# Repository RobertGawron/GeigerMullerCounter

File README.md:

# GeigerMullerCounter

## Purpose

The Geiger–Müller counter is a simple, reliable tool designed to measure ionizing radiation. It is widely used in experiments, radiation detection, and environmental monitoring.

## Principle of Operation
When a high voltage (typically 380–420V) is applied to the Geiger–Müller tube, the tube does not conduct electricity under normal conditions. However, when a radiation particle interacts with the tube, it briefly conducts a current, producing a pulse. These pulses are counted by the detector, and the number of pulses in a given time interval (typically 20 seconds to 2.5 minutes) is proportional to the level of ionizing radiation.

## Final Version
Below is an image of the device (the green PCB in the center). Other components in the image are not relevant to this project, as they belong to the [Cosmic Ray Detector](https://github.com/RobertGawron/CosmicRayDetector), where the Geiger counter is used as a building block.

## System Architecture

The diagram shows the main components and how they interact. The component IDs in parentheses match those in the circuit diagram below, making it easier to understand the circuit.

Tools: PlantUML

## Hardware 

The circuit is shown below. For a full-size image, right-click and open it in a new tab.

Tools: KiCad (for PCB design).

More info can be fond in [here](Hardware/GeigerMullerCounter/README.md).

## Software

Data from the Geiger–Müller counter is collected and managed using the [HardwareDataLogger](https://github.com/RobertGawron/HardwareDataLogger), which is built around an STM32 microcontroller for data collection, display, and storage (via SD card), and an ESP8266 for WiFi communication.

Tools: C++, Python.

## Experiments Conducted

* [Measuring Nuclear Radiation of Potassium from Cigarette Ashes](https://robertgawron.blogspot.com/2015/07/measuring-radioactivity-of-potassium.html): Cigarette ashes are the burnt remains of tobacco leaves, which are rich in potassium. In natural environments, potassium contains the radioactive isotope potassium-40 (K-40), which contributes to the measured radiation levels.
* [Cosmic Ray Detector](https://github.com/RobertGawron/CosmicRayDetector): a device designed to detect high-energy particles, known as cosmic rays, that originate from outer space.
* [Trip to Śnieżka mountain to measure radioactivity levels](https://robertgawron.blogspot.com/2015/06/a-trip-with-geiger-counter-on-sniezka.html): mountains naturally have elevated radiation levels due to increased cosmic rays and radioactive minerals in the rocks. Additionally, near Śnieżka Mountain, a Cold War-era uranium mine in Kowary contributed to the region's historical radiation levels.

## Safety Hazards

**Warning: The device operates at high voltage (380–420V). Contact with the PCB or Geiger tube while powered can cause electric shocks, injuries, or even death. Do not touch any components while the device is powered on.**

## License
This project is licensed under the MIT License. See the [LICENSE](./LICENSE) file for details.

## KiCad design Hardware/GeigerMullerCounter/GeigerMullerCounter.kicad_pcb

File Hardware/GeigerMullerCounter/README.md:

## Introduction

For more details about the hardware design and implementation, visit my [blog post on the Geiger–Müller counter](http://robertgawron.blogspot.com/2015/02/homemade-geigermuller-counter-part-i.html).

# Remarks

Depending on the coil you used, you may need to adjust R3, R4, and R5. If the voltage is too low, try decreasing R4 first.

## KiCad Configuration

To ensure proper alignment and design consistency in KiCad, configure the grid settings as shown below:

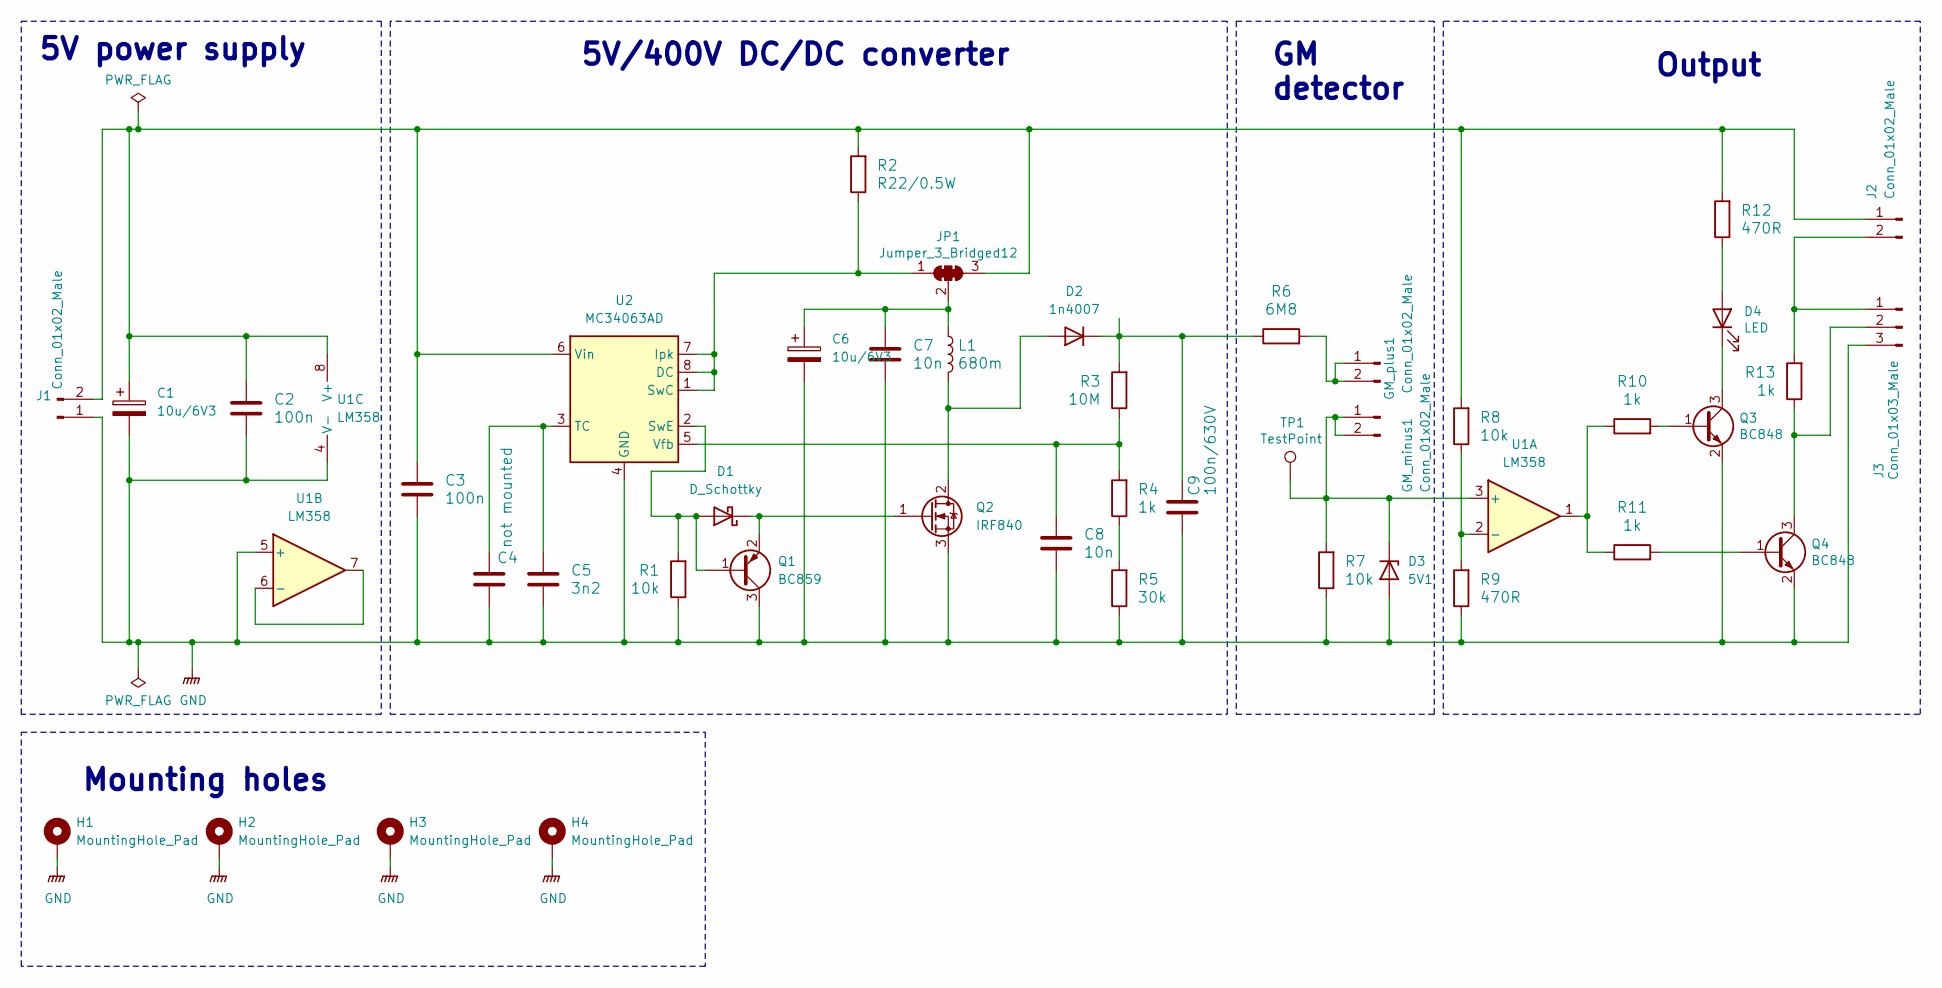
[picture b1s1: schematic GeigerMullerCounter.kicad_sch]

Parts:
C1, C6: 10u/6V3; CP_EIA-3528-21_Kemet-B
C2, C3: 100n; C_0805_2012Metric
C4: not mounted; C_0805_2012Metric
C5: 3n2; C_0805_2012Metric
C7, C8: 10n; C_0805_2012Metric
C9: 100n/630V; C_Rect_L13.5mm_W5.0mm_P10.00mm_FKS3_FKP3_MKS4
D1: D_Schottky; D_SOT-23_ANK
D2: 1n4007; D_DO-41_SOD81_P7.62mm_Horizontal
D3: 5V1; D_A-405_P2.54mm_Vertical_KathodeUp
D4: LED; LED_0805_2012Metric
GM_minus1: Conn_01x02_Male; Pin_Header_Straight_1x02_Pitch2.54mm
GM_plus1: Conn_01x02_Male; Pin_Header_Straight_1x02_Pitch2.54mm
H1, H2, H3, H4: MountingHole_Pad; MountingHole_3.5mm_Pad
J1, J2: Conn_01x02_Male; PinHeader_1x02_P2.54mm_Vertical
J3: Conn_01x03_Male; PinHeader_1x03_P2.54mm_Vertical
JP1: Jumper_3_Bridged12; SolderJumper-3_P1.3mm_Bridged12_Pad1.0x1.5mm
L1: 680m; L_Radial_D7.5mm_P5.00mm_Fastron_07P
Q1: BC859; TSOT-23
Q2: IRF840; TO-220-3_Vertical
Q3, Q4: BC848; SOT-23
R1, R8: 10k; R_0805_2012Metric
R2: R22/0.5W; R_Axial_DIN0207_L6.3mm_D2.5mm_P2.54mm_Vertical
R3: 10M; R_Axial_DIN0207_L6.3mm_D2.5mm_P5.08mm_Vertical
R4, R10, R11, R13: 1k; R_0805_2012Metric
R5: 30k; R_0805_2012Metric
R6: 6M8; R_Axial_DIN0207_L6.3mm_D2.5mm_P7.62mm_Horizontal
R7: 10k; R_0805_2012Metric_Pad1.15x1.40mm_HandSolder
R9, R12: 470R; R_0805_2012Metric
TP1: TestPoint; TestPoint_Pad_D1.5mm
U1: LM358; SO-8_5.3x6.2mm_P1.27mm
U2: MC34063AD; SO-8_5.3x6.2mm_P1.27mm

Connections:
GND: C1.2, C2.2, C3.2, C4.2, C5.2, C6.2, C7.2, C8.2, C9.2, D3.2 (A), H1.1, H2.1, H3.1, H4.1, J1.1, J3.3, Q1.3 (C), Q2.3 (S), Q3.2 (E), Q4.2 (E), R1.1, R5.1, R7.1, R9.1, U1.4 (V-), U1.5 (+), U2.4 (GND)
unnamed: D1.2 (A), Q1.1 (B), R1.2, U2.2 (SwE)
unnamed: D1.1 (K), Q1.2 (E), Q2.1 (G)
unnamed: D2.2 (A), L1.2, Q2.2 (D)
unnamed: C9.1, D2.1 (K), R3.2, R6.1
unnamed: D3.1 (K), GM_minus1.1, GM_minus1.2, R7.2, TP1.1, U1.3 (+)
unnamed: D4.2 (A), R12.1
unnamed: D4.1 (K), Q3.3 (C)
unnamed: GM_plus1.1, GM_plus1.2, R6.2
unnamed: C1.1, C2.1, C3.1, J1.2, J2.1, JP1.3 (B), R2.2, R8.2, R12.2, U1.8 (V+), U2.6 (Vin)
unnamed: J2.2, J3.1, R13.2
unnamed: J3.2, Q4.3 (C), R13.1
unnamed: JP1.1 (A), R2.1, U2.1 (SwC), U2.7 (Ipk), U2.8 (DC)
unnamed: C6.1, C7.1, JP1.2 (C), L1.1
unnamed: Q3.1 (B), R10.2
unnamed: Q4.1 (B), R11.2
unnamed: R4.1, R5.2
unnamed: R10.1, R11.1, U1.1
unnamed: R8.1, R9.2, U1.2 (-)
unnamed: U1.6 (-), U1.7
unnamed: C4.1, C5.1, U2.3 (TC)
unnamed: C8.1, R3.1, R4.2, U2.5 (Vfb)

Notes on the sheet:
Mounting holes
Output
5V/400V DC/DC converter
GM detector
5V power supply

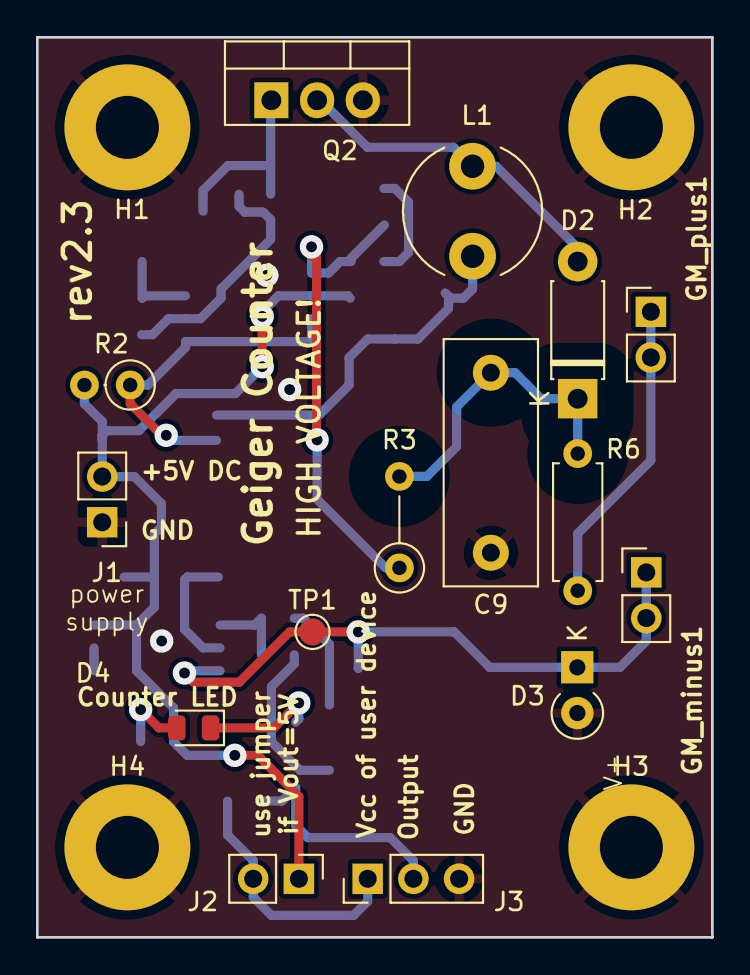
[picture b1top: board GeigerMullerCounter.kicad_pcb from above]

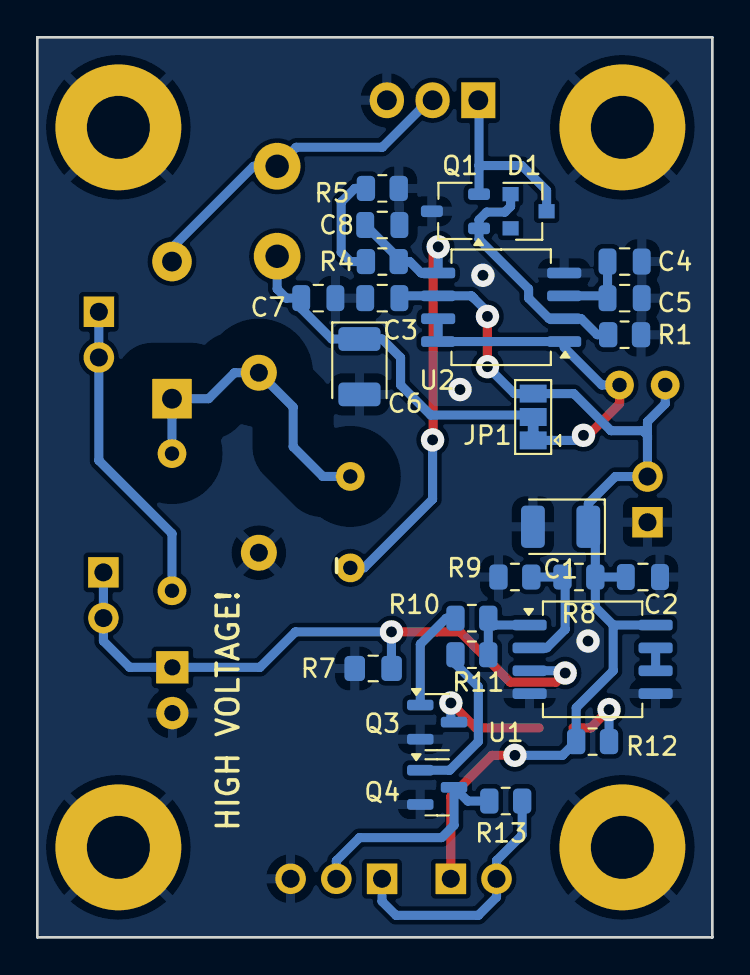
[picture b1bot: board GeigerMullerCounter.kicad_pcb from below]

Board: 2 copper layers, 37.5 x 50.0 mm, 44 parts (25 on the bottom side), 22 nets.

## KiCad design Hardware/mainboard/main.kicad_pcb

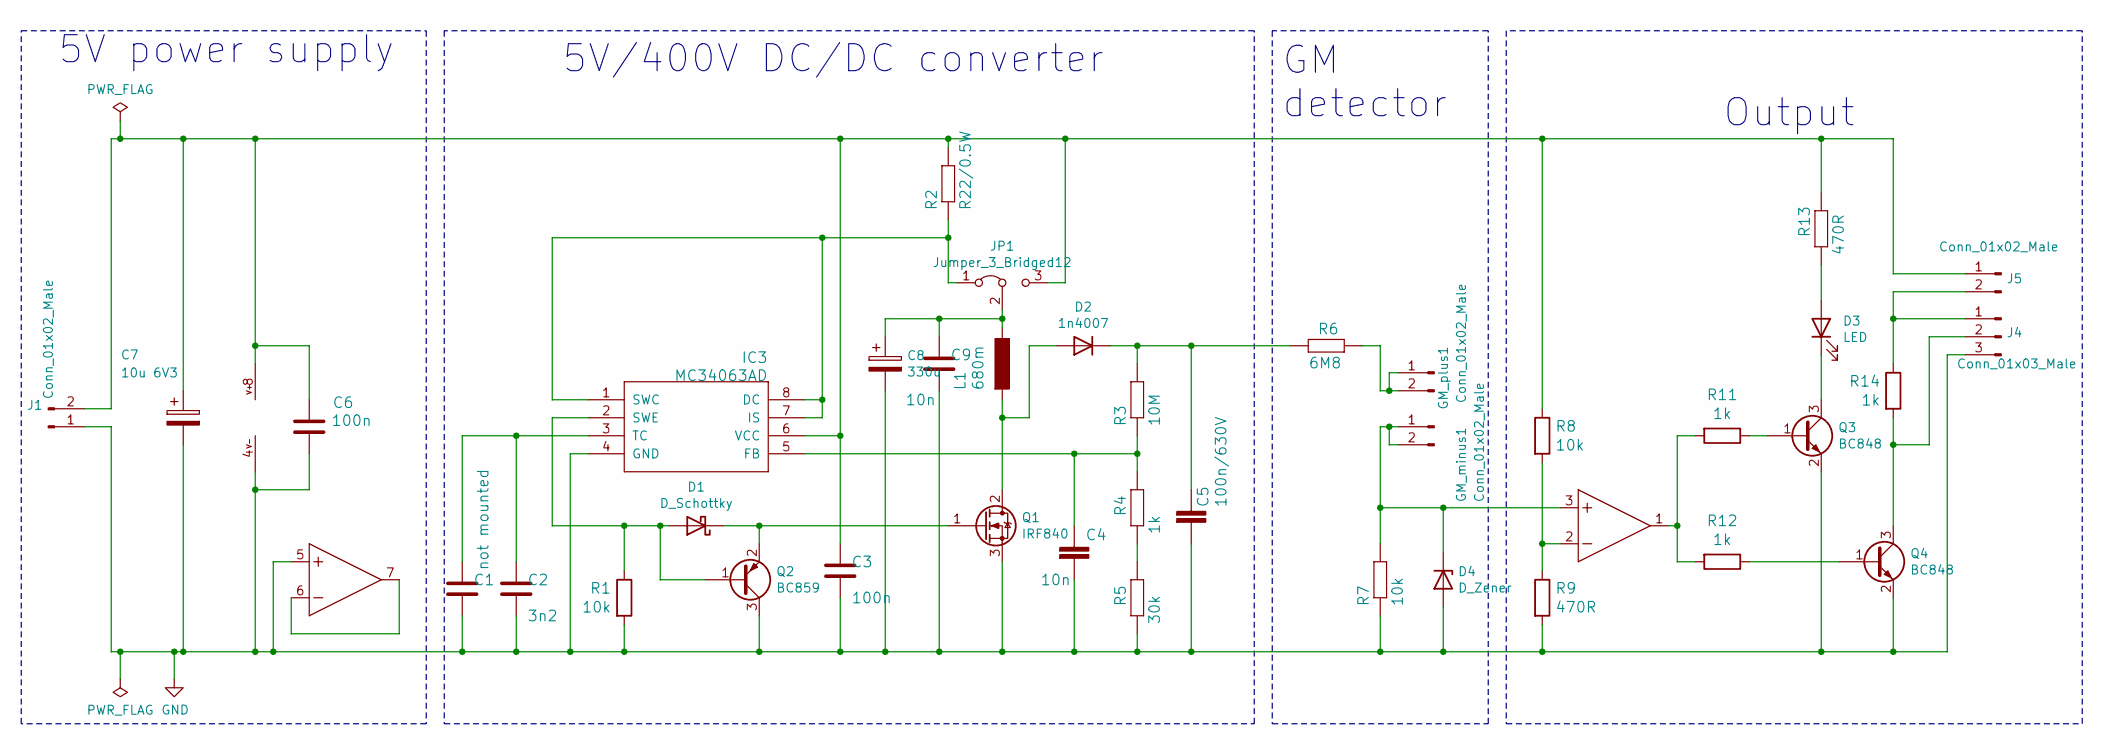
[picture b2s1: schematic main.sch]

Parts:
C1: not mounted; C_0805_2012Metric_Pad1.15x1.40mm_HandSolder
C2: 3n2; C_0805_2012Metric_Pad1.15x1.40mm_HandSolder
C3, C6: 100n; C_0805_2012Metric_Pad1.15x1.40mm_HandSolder
C4, C9: 10n; C_0805_2012Metric_Pad1.15x1.40mm_HandSolder
C5: 100n/630V; C_Rect_L13.5mm_W5.0mm_P10.00mm_FKS3_FKP3_MKS4
C7: 10u 6V3; CP_EIA-3528-21_Kemet-B
C8: 330u; CP_EIA-3528-21_Kemet-B
D1: D_Schottky; D_SOT-23_ANK
D2: 1n4007; D_DO-41_SOD81_P7.62mm_Horizontal
D3: LED; LED_D3.0mm
D4: D_Zener; D_A-405_P2.54mm_Vertical_KathodeUp
GM_minus1: Conn_01x02_Male; Pin_Header_Straight_1x02_Pitch2.54mm
GM_plus1: Conn_01x02_Male; Pin_Header_Straight_1x02_Pitch2.54mm
IC2: LM358D; SO-8_5.3x6.2mm_Pitch1.27mm
IC3: MC34063AD; SO-8_5.3x6.2mm_Pitch1.27mm
J1, J5: Conn_01x02_Male; Pin_Header_Straight_1x02_Pitch2.54mm
J4: Conn_01x03_Male; Pin_Header_Straight_1x03_Pitch2.54mm
JP1: Jumper_3_Bridged12; SolderJumper-3_P1.3mm_Bridged12_Pad1.0x1.5mm
L1: 680m; L_Radial_D7.5mm_P5.00mm_Fastron_07P
Q1: IRF840; TO-220-3_Vertical
Q2: BC859; SOT-23
Q3, Q4: BC848; SOT-23
R1, R7, R8: 10k; R_0805_2012Metric_Pad1.15x1.40mm_HandSolder
R2: R22/0.5W; R_Axial_DIN0207_L6.3mm_D2.5mm_P2.54mm_Vertical
R3: 10M; R_Axial_DIN0207_L6.3mm_D2.5mm_P5.08mm_Vertical
R4, R11, R12, R14: 1k; R_0805_2012Metric_Pad1.15x1.40mm_HandSolder
R5: 30k; R_0805_2012Metric_Pad1.15x1.40mm_HandSolder
R6: 6M8; R_Axial_DIN0207_L6.3mm_D2.5mm_P7.62mm_Horizontal
R9, R13: 470R; R_0805_2012Metric_Pad1.15x1.40mm_HandSolder

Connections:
GND: C1.2, C2.2, C3.2, C4.2, C5.2, C6.2, C7.2, C8.2, C9.2, D4.2 (A), IC2.4 (V-), IC2.5 (+IN), IC3.4 (GND), J1.1, J4.3, Q1.3 (S), Q2.3 (C), Q3.2 (E), Q4.2 (E), R1.2, R5.1, R7.1, R9.2
unnamed: C1.1, C2.1, IC3.3 (TC)
unnamed: C3.1, C6.1, C7.1, IC2.8 (V+), IC3.6 (VCC), J1.2, J5.1, JP1.3 (B), R2.2, R8.1, R13.2
unnamed: C4.1, IC3.5 (FB), R3.1, R4.2
unnamed: C5.1, D2.1 (K), R3.2, R6.1
unnamed: C8.1, C9.1, JP1.2 (C), L1.1
unnamed: D1.1 (K), Q1.1 (G), Q2.2 (E)
unnamed: D1.2 (A), IC3.2 (SWE), Q2.1 (B), R1.1
unnamed: D2.2 (A), L1.2, Q1.2 (D)
unnamed: D3.1 (K), Q3.3 (C)
unnamed: D3.2 (A), R13.1
unnamed: D4.1 (K), GM_minus1.1, GM_minus1.2, IC2.3 (+IN), R7.2
unnamed: GM_plus1.1, GM_plus1.2, R6.2
unnamed: IC2.1 (OUT), R11.2, R12.2
unnamed: IC2.2 (-IN), R8.2, R9.1
unnamed: IC2.6 (-IN), IC2.7 (OUT)
unnamed: IC3.1 (SWC), IC3.7 (IS), IC3.8 (DC), JP1.1 (A), R2.1
unnamed: J4.1, J5.2, R14.1
unnamed: J4.2, Q4.3 (C), R14.2
unnamed: Q3.1 (B), R11.1
unnamed: Q4.1 (B), R12.1
unnamed: R4.1, R5.2

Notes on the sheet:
5V power supply
5V/400V DC/DC converter
GM detector
Output

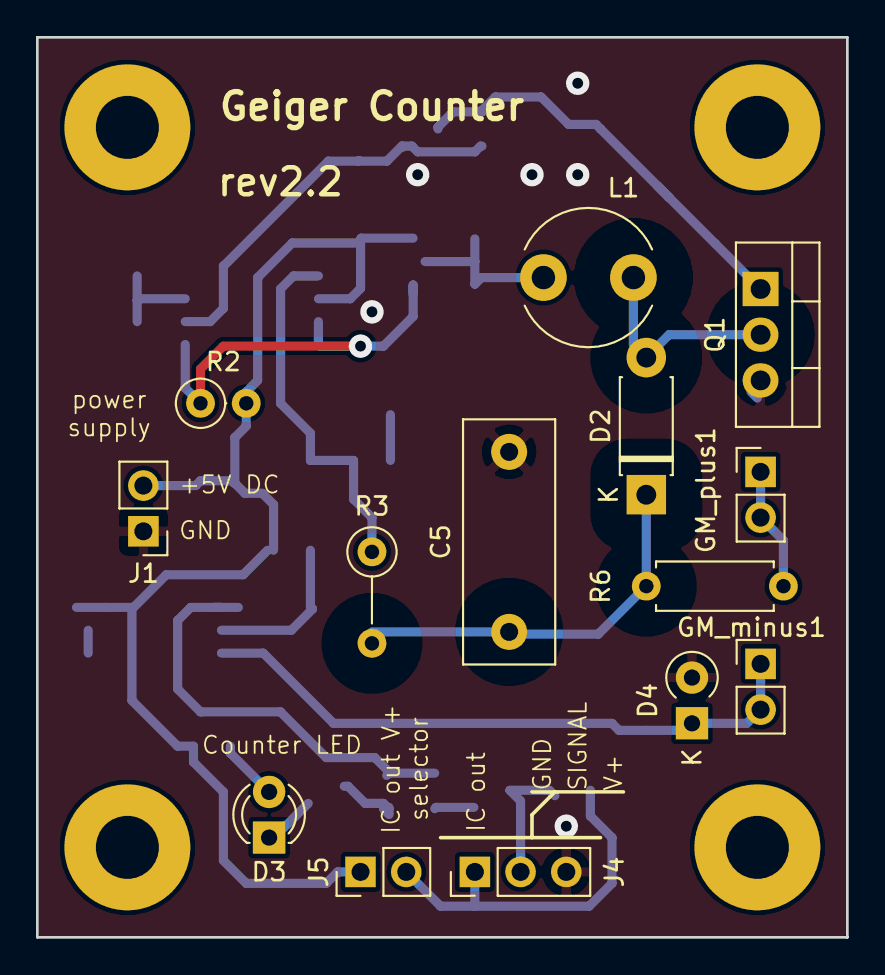
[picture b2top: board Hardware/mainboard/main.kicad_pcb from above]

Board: 2 copper layers, 45.0 x 50.0 mm, 39 parts (0 on the bottom side), 22 nets.

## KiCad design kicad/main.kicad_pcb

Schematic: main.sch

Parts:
C1, C2: 32n; C_0805_HandSoldering
C3, C6: 100n; C_0805_HandSoldering
C4: 10n; C_0805_HandSoldering
C5: 100n/630V; C_Axial_L12.0mm_D7.5mm_P15.00mm_Horizontal
C7: 330u; CP_Tantalum_Case-B_EIA-3528-21_Hand
D1: D_Schottky; D_SOT-23_ANK
D2: 1n4007; D_DO-41_SOD81_P7.62mm_Horizontal
D3: LED; LED_D3.0mm
IC2: LM358D; SO-8_5.3x6.2mm_Pitch1.27mm
IC3: MC34063AD; SO-8_5.3x6.2mm_Pitch1.27mm
J1: Power; Pin_Header_Angled_1x02_Pitch2.54mm
J2: GM Tube; Pin_Header_Angled_1x02_Pitch2.54mm
JP1: JP1E; Pin_Header_Straight_1x02_Pitch2.54mm
L1: 680m; L_Radial_D7.5mm_P5.00mm_Fastron_07P
Q1: IRF840; TO-220-3_Vertical
Q2: Q_PNP_BEC; SOT-23
Q3, Q4: BC848SMD; SOT-23
R1: 10k; R_0805_HandSoldering
R2: R22/0.5W; R_Axial_DIN0207_L6.3mm_D2.5mm_P2.54mm_Vertical
R3: 10M; R_Axial_DIN0207_L6.3mm_D2.5mm_P5.08mm_Vertical
R4, R11, R12, R14: 1k; R_0805_HandSoldering
R5: 30k; R_0805_HandSoldering
R6: 6M8; R_Axial_DIN0207_L6.3mm_D2.5mm_P5.08mm_Vertical
R7: 10k; R_Axial_DIN0207_L6.3mm_D2.5mm_P2.54mm_Vertical
R8: ?; R_0805_HandSoldering
R9: 470R; R_0805_HandSoldering
R13: 510R; R_0805_HandSoldering
SV2: Digital Output; Pin_Header_Straight_1x03_Pitch2.54mm

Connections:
GND: C1.2, C2.2, C3.2, C4.2, C5.2, C6.2, C7.2, IC2.4 (V-), IC2.5 (+IN), IC3.4 (GND), J1.1, Q1.3 (S), Q2.2 (E), Q3.2 (E), Q4.2 (E), R1.1, R5.1, R7.1, R9.1, SV2.1
unnamed: C1.1, C2.1, IC3.3 (TC)
unnamed: C3.1, C6.1, C7.1, IC2.8 (V+), IC3.6 (VCC), J1.2, JP1.1, R2.2, R8.2, R13.2
unnamed: C4.1, IC3.5 (FB), R3.1, R4.2
unnamed: C5.1, D2.1 (K), R3.2, R6.1
unnamed: D1.1 (K), Q1.1 (G), Q2.3 (C)
unnamed: D1.2 (A), IC3.2 (SWE), Q2.1 (B), R1.2
unnamed: D2.2 (A), L1.2, Q1.2 (D)
unnamed: D3.1 (K), Q3.3 (C)
unnamed: D3.2 (A), R13.1
unnamed: IC2.1 (OUT), R11.1, R12.1
unnamed: IC2.2 (-IN), R8.1, R9.2
unnamed: IC2.3 (+IN), J2.2, R7.2
unnamed: IC2.6 (-IN), IC2.7 (OUT)
unnamed: IC3.1 (SWC), IC3.7 (IS), IC3.8 (DC), L1.1, R2.1
unnamed: J2.1, R6.2
unnamed: JP1.2, R14.2, SV2.3
unnamed: Q3.1 (B), R11.2
unnamed: Q4.1 (B), R12.2
unnamed: Q4.3 (C), R14.1, SV2.2
unnamed: R4.1, R5.2

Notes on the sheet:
Power supply
5V/400V DC/DC converter
GM detector
Output

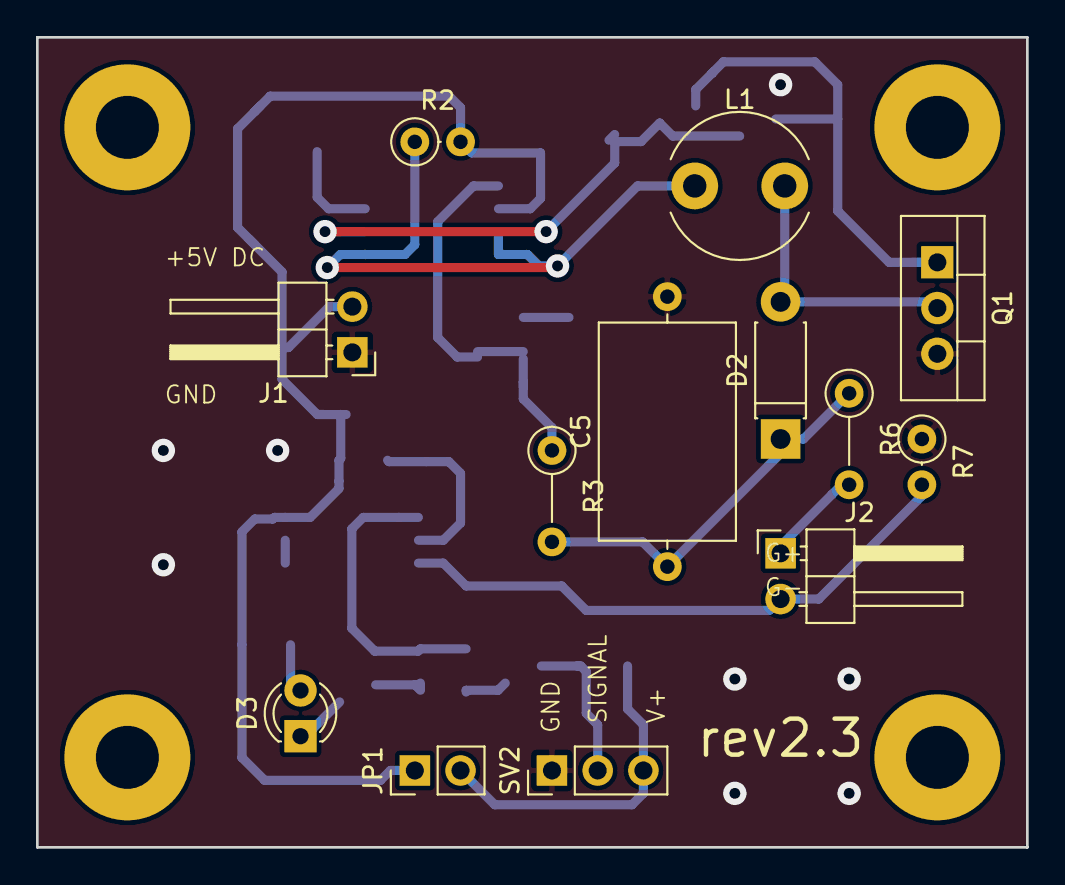
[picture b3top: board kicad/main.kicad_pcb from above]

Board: 2 copper layers, 55.0 x 45.0 mm, 34 parts (0 on the bottom side), 21 nets.

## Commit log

2014-06-13 Morged stuff from my other project ( https://github.com/RobertGawron/ArduinoAnts )
2014-12-21 IAR implementation removed.
2014-12-21 Empty CooCox project.
2014-12-21 Removed unused files.
2014-12-21 Possible to display messages on LCD.
2014-12-21 Dummy data presented on LCD.
2014-12-21 Code formating.
2014-12-21 Touch LCD sensor added.
2014-12-21 Added drawing a simple graph.
2014-12-22 Draft of layout manager.
2014-12-22 Files renamed, methods names changed.
2014-12-22 Files rename.
2014-12-22 Added #ifndef #define #endif trinity.
2014-12-22 Added #ifndef ... trinity, code cleanup.
2014-12-23 Added layout generated specific files.
2014-12-23 Added real intro layout.
2014-12-26 Stub for temperature sensor.
2014-12-26 Draft of temperature sensor (reading from GPIO).
2014-12-26 Types from inttypes.h used everywhere.
2015-04-04 HW project added. Directory structure changed.
2015-04-04 Fixed directory structure.
2015-04-04 Removed unused code.
2015-04-04 Fixed project name.
2015-04-04 Fixed description of the project.
2015-04-04 Removed touch sensor code.
2015-04-04 Working version.
2015-04-04 Fixed PCB.
2015-05-27 Version with new step-up driver.
2015-06-14 Built and tested version.
2015-06-14 Tested version.
2015-06-14 Fixed as is on HW model.
2015-06-17 LCD and GPIO code moved to separate files.
2015-06-17 Indentation fixed.
2015-06-18 Folder structure changed.
2015-06-18 Software relase v1.0
2015-06-18 HW version 2.2
2015-06-28 Extended directory structure.
2015-06-28 Project structure modification.
2015-06-28 Fixed uppercase in directory name.
2015-06-28 Added README.
2015-06-28 Added PC visualization of received data.
2015-07-01 Counts handling moved to new .h/.c files.
2015-07-01 Added missing changes.
2015-07-04 Issue #4 fixed.
2015-07-04 Feature #1 in progress.
2015-07-04 Refactoring for #1.
2015-07-05 Refactoring needed for #1 in progress.
2015-07-05 Further refactoring needed for #1.
2015-07-05 Final version of the refactoring for #1
2015-07-05 Feature #1 resolve.
2015-07-05 Issue #11 fixed.
2015-07-05 Issue #8 fixed.
2015-07-13 PCB for GM connectors.
2015-07-13 Top description layer added.
2015-07-13 Fixed bug in displaying results.
2015-07-15 After first prototype.
2015-07-29 P-Star 25K50 Micro peoject added.
2015-07-29 P-Star25K50 Micr: added missing files.
2015-07-29 Project structure update.
2015-07-29 README updated by project setup howto.
2015-07-29 USB drivers added.
2016-07-24 Removed obsolete fimware.
2016-07-24 Arduino software version.
2016-07-24 Removed pointless files.
2016-07-24 Fixing dir structure.
2016-07-24 Fixinf dir structure part 2.
2016-08-16 Changed LCD pins.
2016-08-16 Arduino shield added.
2016-08-16 Fixed resistor value.
2016-08-16 Histogram bins fix.
2016-08-16 Bin counting fix.
2016-08-16 Debouncing works a bit better.
2016-08-26 Fixed key handling. Extended Welcome Layout.
2016-08-26 Fixed switching between layouts.
2016-08-26 removed whitespaces.
2016-08-26 Primitive implementation of uSv/h dosage.
2016-08-26 Fixed uSv/h conversion.
2016-08-27 Historgram and cpm to uSv/h fixes.
2017-01-08 Fixes in arduino shield.
2018-05-27 PCB is now fixed.
2018-09-09 local libraries added
2018-09-09 moved to eclipse
2018-09-09 fixed project structure
2018-09-13 keyboard support
2018-09-13 remove impl of Layout class
2018-09-13 draft of layouts stuff
2018-09-13 draft of pulse layout
2018-09-13 cleanup
2018-09-13 fix in sample buffer
2018-09-13 class rename
2018-09-13 split function
2018-09-13 default constructors
2018-09-13 class to handle layouts
2018-09-13 impl of layout handler class
2018-09-13 refactor how measurements are stored
2018-09-13 method variable name refactor
2018-09-13 class name change
2018-09-13 class splited to a sparate file
2018-09-13 comments
2018-09-13 whitespace
2018-09-14 implementation of the buffer
2018-09-14 infinitive loop for event handling
2018-09-15 fixed circular buffer
2018-09-15 remove arduino ide based project
2018-09-15 directory rename
2018-09-15 fixed footprint place
2018-09-19 folder for eagle version
2018-09-19 kicad version of main pcb
2018-09-19 Create LICENSE
2018-09-19 component placement fix
2018-09-19 add missing gerber file
2018-09-19 even more missing files added
2018-09-19 elements placement fix
2018-09-19 drc check ok
2018-09-20 directory structure change
2019-02-16 draft for the stm32 firmware
2019-02-16 new hw ready to be send to pcb company
2019-02-16 folder structure cleanup
2019-02-17 remove obsolete kicad projects
2019-02-17 fixes after hw tests
2019-03-24 warnings threated as errors
2019-03-24 fixed index error
2019-03-24 label to display dosage
2019-03-24 fixed extern
2019-03-24 added serial port files
2019-03-24 com port moved to sparate file
2019-06-04 removed junk files, added gitignore
2019-06-04 removed cache reference
2019-06-04 removed gm connector and arduino projects
2019-06-08 cleaned up include structure
2019-06-16 sw from my old arduino project as a draft
2019-06-16 working arduino sw firmware
2019-06-16 pcb for gm counter, gm tube connector and arduino
2019-06-16 refactored code
2019-06-16 moved from eagle to kicad
2019-06-16 stm32 fimware
2019-06-16 added more detailed readme
2019-08-11 unified with my other repositories
2019-08-11 architecture documents
2019-08-11 remove junk text
2019-08-11 fix label place
2019-08-11 added warning about hv
2019-08-11 champter rename
2019-08-11 travis to check latex generation
2019-08-11 add CI status
2019-08-11 fixed formatting
2020-06-06 use kicad elments (after eagle to kicad transition)
2020-09-12 add suport for vscode build
2020-09-12 add makefile
2020-09-12 update of cubemx project
2020-09-12 possible to compile and flash, not posssible to debug, or use vscode key bindings
2020-09-13 add bindings for build and flashing, note: this file must be copied to C:\Users\USER_NAME\AppData\Roaming\Code\User\keybindings.json and is shared between all projects
2020-10-09 draft + working timer
2020-10-09 added logger
2020-10-09 add circular buffer
2020-10-09 add display logic (no hw implementation)
2020-10-09 add display hw impolementation and meassurement calculator
2020-10-09 add missing component initialization
2020-10-09 code cleanup
2020-10-09 remove project for older board version
2020-10-10 fixed logger timer to 60s
2020-10-10 split hw and application logic of logger
2020-10-10 add extra compilation warning flags, not all are possible to be enabled as errors due to implementation of HAL and LCD library (that I don't want to modify)
2020-10-10 Squashed 'Test/UnitTest/UTestLib/' content from commit 9e4f32de
    git-subtree-dir: Test/UnitTest/UTestLib
    git-subtree-split: 9e4f32de20710bff2ad0b6dd70e9ae14fbe16c11
2020-10-10 add dummmy tests
2020-10-11 basic tests structure
2020-10-11 part of unit tests for GMCircularBuffer_GetElement
2020-10-12 fixed args order
2020-10-12 firmware can be now compiled to .exe
2020-10-12 add python bindings
2020-10-13 add draft of gui for simulator
2020-10-13 add draft of hw display simulation
2020-10-14 hw display implementation
2020-10-15 fully working versionr
2020-10-15 remove files moved to new repo
2020-10-15 Squashed 'Software/Firmware/' content from commit 37d90c36
    git-subtree-dir: Software/Firmware
    git-subtree-split: 37d90c36ef6dff2428dff3a75682a6a990aea3fe
2020-10-15 cleanup after moving firmware to separate repo
2020-10-17 remove old version
2020-10-17 Squashed 'Software/HardwareDataLogger/' content from commit 36e64a0b
    git-subtree-dir: Software/HardwareDataLogger
    git-subtree-split: 36e64a0b74689bc3145da8180f2f13aac98a8adf
2020-10-23 move from travis to github actions, move ,gitignore for Kicad files into hardware directory
2020-10-23 link build status to project's build section
2020-10-24 move (for diagrams) from .png to .svg
2020-10-24 move (for diagrams) from .png to .svg - add missing .svg file
2020-10-24 Squashed 'Software/HardwareDataLogger/' changes from 36e64a0b..dc3c36eb
    dc3c36eb Merge pull request #21 from RobertGawron/develop
    a8342c6a Merge pull request #20 from RobertGawron/feature/add_contionous_integration
    304d8cda fix c linter issues
    4a7e1a6d Merge pull request #19 from RobertGawron/develop
    1880f227 Merge pull request #18 from RobertGawron/feature/add_contionous_integration
    7c2c33d9 exclude external libs from repo programming language statistics
2020-11-06 Add info about zener diode voltage (#89)
2020-11-06 Fix grammar mistakes (found by Code Spell Checker add-on in VSCode). (fix #100)
2020-11-06 Squashed 'Software/HardwareDataLogger/' changes from dc3c36eb..58e2b477
    58e2b477 Merge pull request #24 from RobertGawron/develop
    74d71741 Merge pull request #23 from RobertGawron/fix/remove_gammar_mistakes
    8752828e Fix grammar mistakes (found by Code Spell Checker add-on in VSCode). (fix #22)
    git-subtree-dir: Software/HardwareDataLogger
    git-subtree-split: 58e2b477f2824c01ec6d98d952829f0472e2d4a0
2024-09-09 add image of the device and fix url in readme
2024-09-13 hw revision 2.3
